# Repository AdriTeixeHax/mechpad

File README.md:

# :snowflake:Project MechPad:fire:
DIY, modular, split, open source mechanical keyboard and macro-pad with per-key RGB lighting, built around the ATMEGA-32U4 microcontroller.

## Features:
- Open source design.
- Swappable cherry-style mechanical switches.
- Aluminum casing.
- Modular design: detachable macro-pad with more room for expansion, attachable via magnets placed around the keyboard case.
- Rotary encoders to toggle programmable events, such as volume control or timeline scrolling for video editing software.
- OLED screen which displays layout information, battery status and other custom functions.
- Bluetooth integration.
- Easily swappable Li-Ion battery.
- Integrated 4-port USB hub, with downstream USB-A and USB-C ports.
- Per-key RGB lighting using WS2812(B) 5050 SMD LEDs.
- Ice-fire aesthetic.

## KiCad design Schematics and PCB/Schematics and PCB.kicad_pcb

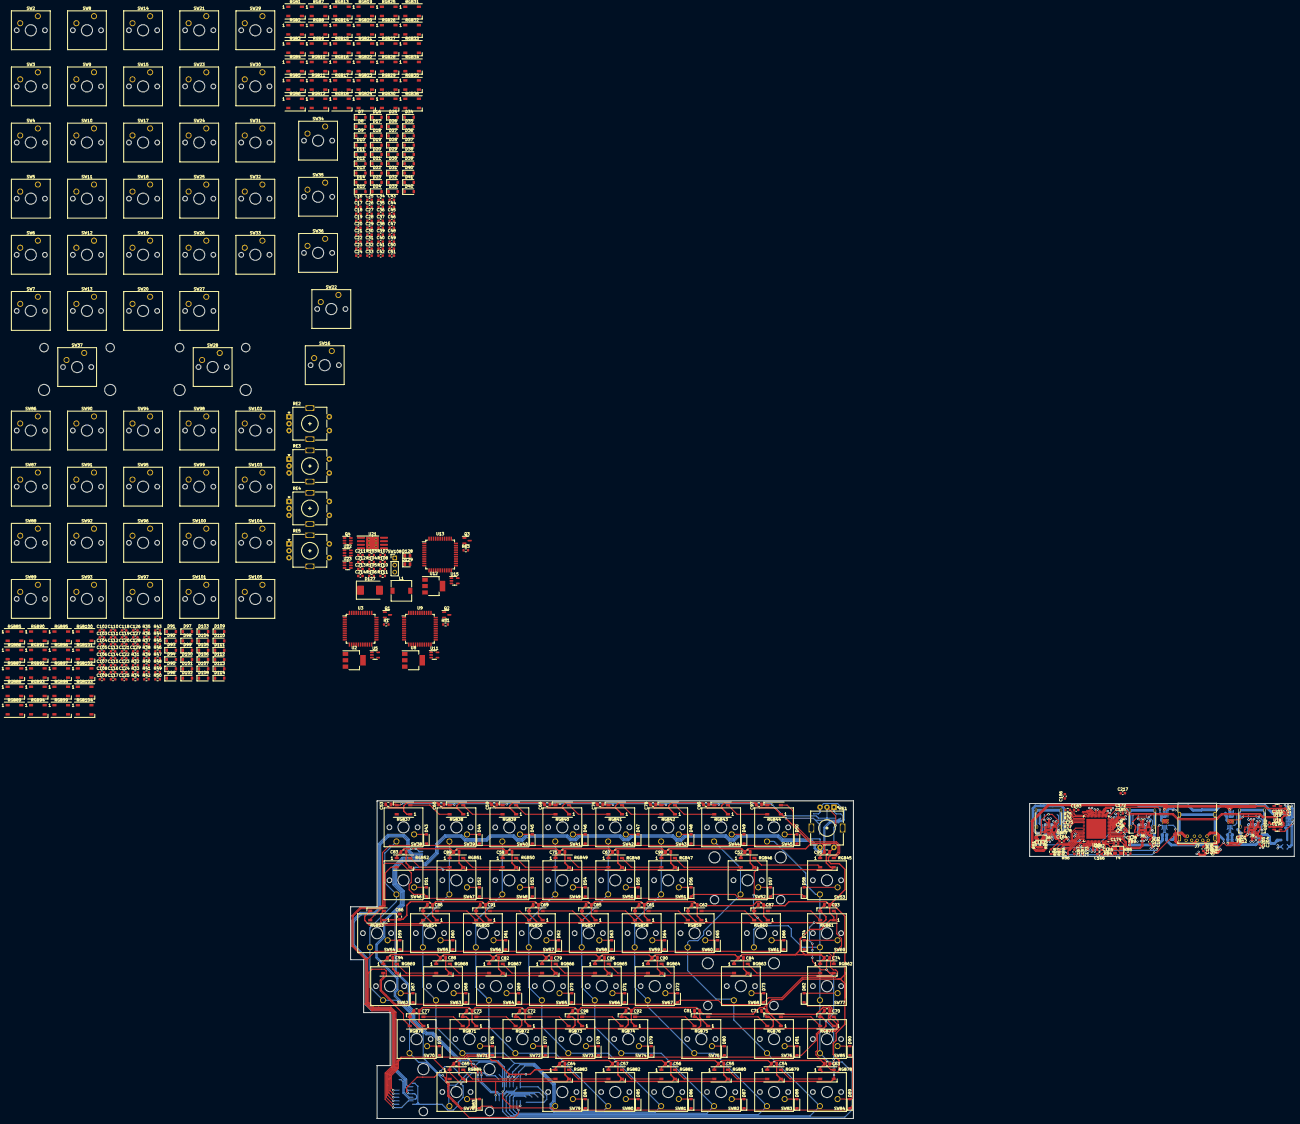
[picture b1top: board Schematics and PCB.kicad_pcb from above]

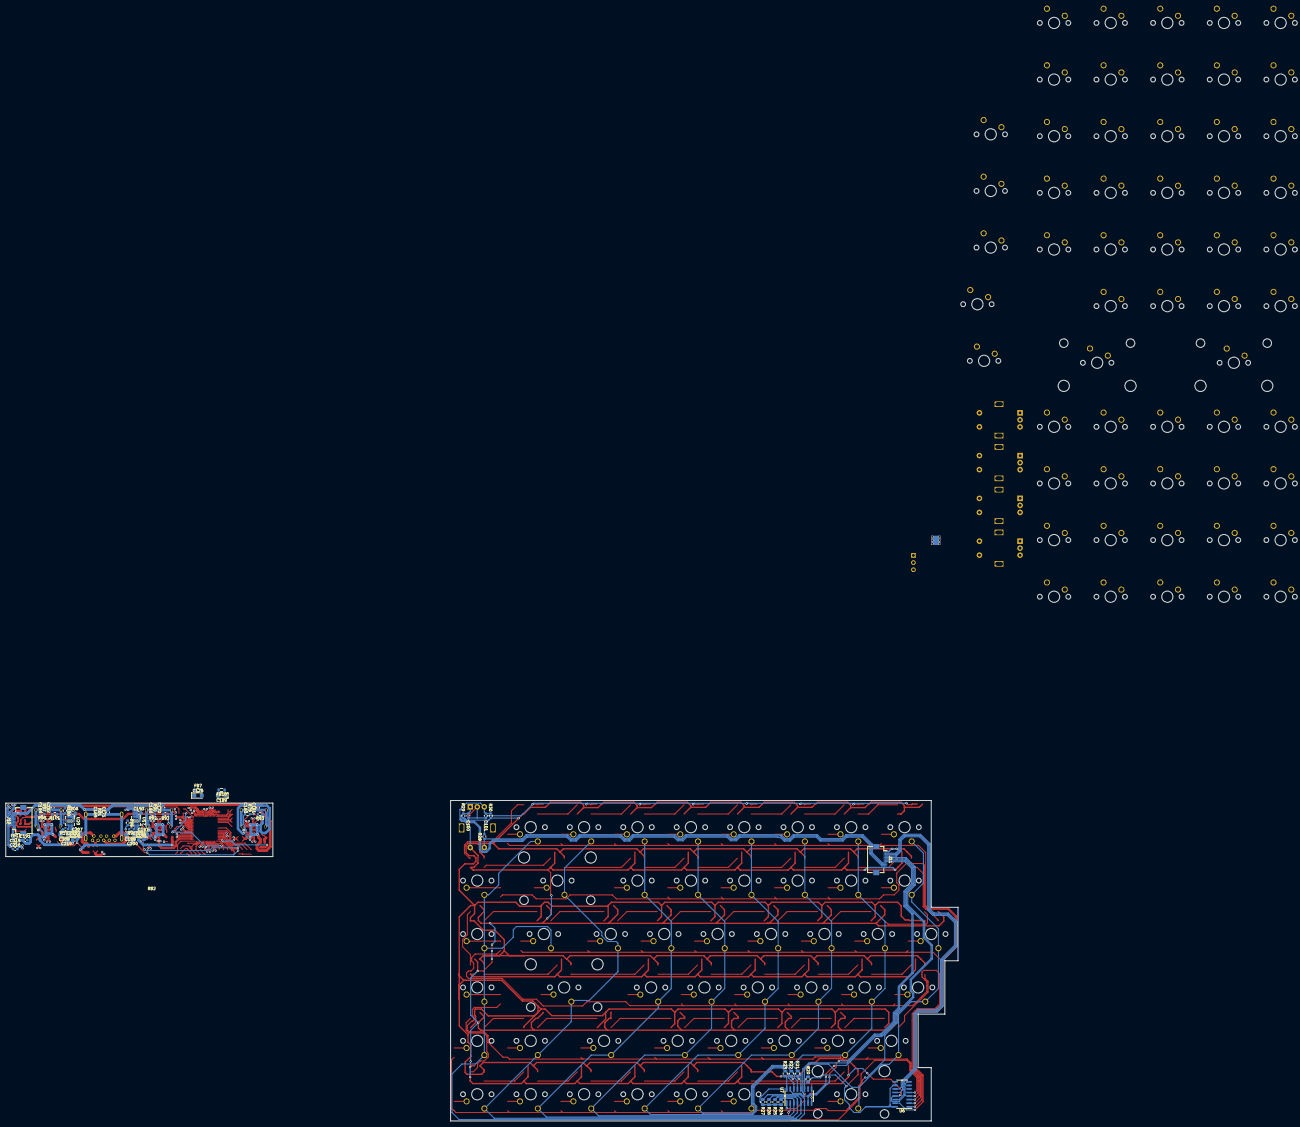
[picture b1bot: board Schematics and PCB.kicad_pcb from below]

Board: 4 copper layers, 339.6 x 114.3 mm, 604 parts (61 on the bottom side), 390 nets.

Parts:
C16, C17, C18, C19, C20, C21, C22, C23, C24, C25, C26, C27, C28, C29, C30, C31, C32, C33, C34, C35, C36, C37, C38, C39, C40, C41, C42, C43, C44, C45, C46, C47, C48, C49, C50, C51, C100, C101, C102, C103, C104, C105, C106, C107, C108, C109, C110, C111, C112, C113, C114, C115, C116, C117, C118, C119, C120, C121, C161, C163, C164, C170, C171, C172, C173, C174, C175, C177, C178, C179, C180, C181, C182, C183, C184, C185, C186, C187, C188, C190, C191, C193, C194, C198, C200, C201, C204, C205, C206, C208, C210, C214, C215, C216, C217: 100n; C_0603_1608Metric
C52, C53, C54, C55, C56, C57, C58, C59, C60, C61, C62, C63, C64, C65, C66, C67, C68, C69, C70, C71, C72, C73, C74, C75, C76, C77, C78, C79, C80, C81, C82, C83, C84, C85, C86, C87, C88, C89, C90, C91, C92, C93, C94, C95, C96, C97, C98, C99: 100n; C_0805_2012Metric
C122, C123, C124, C125, C126, C127, C128, C129: 10n; C_0603_1608Metric
C160, C168, C169, C192: 1n; C_0603_1608Metric
C162, C176, C189: 10u; CP_EIA-3216-18_Kemet-A
C165, C166: 20p; C_0603_1608Metric
C167: 1u; C_0603_1608Metric
C195, C196, C202, C203: 1u X5R; C_0603_1608Metric
C197, C199, C207, C209: 150u; CP_EIA-3216-18_Kemet-A
C211, C213: 22u; C_0603_1608Metric
C212: 10u; C_0603_1608Metric
D7, D8, D9, D10, D11, D12, D13, D14, D15, D16, D17, D18, D19, D20, D21, D22, D23, D24, D25, D26, D27, D28, D29, D30, D31, D32, D33, D34, D35, D36, D37, D38, D39, D40, D41, D42, D43, D44, D45, D46, D47, D48, D49, D50, D51, D52, D53, D54, D55, D56, D57, D58, D59, D60, D61, D62, D63, D64, D65, D66, D67, D68, D69, D70, D71, D72, D73, D74, D75, D76, D77, D78, D79, D80, D81, D82, D83, D84, D85, D86, D87, D88, D89, D90, D91, D92, D93, D94, D95, D96, D97, D98, D99, D100, D101, D102, D103, D104, D105, D106, D107, D108, D109, D110, D111, D112, D113, D114: 1N4148W; D_SOD-123
D127: SS34; D_SMC
D128: Red; LED_0805_2012Metric
D129: Green; LED_0805_2012Metric
FB7, FB8, FB9, FB10, FB11, FB12: >50mΩ 220Ω @ 100MHz; L_0805_2012Metric
J6: UPSTREAM; USB_C_Receptacle_Amphenol_12401610E4-2A
J7: DOWNSTREAM_3; USB3_A_Molex_48393-001
J8: DOWNSTREAM_1; USB_C_Receptacle_Amphenol_12401610E4-2A
J9: DOWNSTREAM_2; USB_C_Receptacle_Amphenol_12401610E4-2A
J10, J11: Conn_01x12; Hirose_FH12-12S-0.5SH_1x12-1MP_P0.50mm_Horizontal
L1: 22uH; L_7.3x7.3_H4.5
Q1, Q2, Q3: FDN340P; SOT-23
Q4: FS8205; SOT-23-6
R1, R51, R63, R79, R84, R90, R91, R97: 1M; R_0603_1608Metric
R20, R21, R22, R23, R24, R25, R26, R27: 10K; R_0805_2012Metric
R28, R86, R94, R95, R99, R100: 10k; R_0603_1608Metric
R29, R30, R31, R32, R33, R34, R35, R36, R37, R38, R39, R40, R41, R42, R43, R44, R45, R46, R47, R48, R49, R50: 10K; R_0603_1608Metric
R75, R76, R77, R78, R87, R88, R89: 4.7k; R_0603_1608Metric
R80: 90.9kΩ ±1%; R_0603_1608Metric
R81: 10kΩ ±1%; R_0603_1608Metric
R82, R83, R92, R93, R98, R101: 5.1k; R_0603_1608Metric
R85: 9.53kΩ ±1%; R_0603_1608Metric
R96, R102: 25.5k; R_0603_1608Metric
R103: 7.5K; R_0603_1608Metric
R104, R105, R106, R107, R108, R110, R111: 1k; R_0603_1608Metric
RE1, RE2, RE3, RE4, RE5: EC11; RotaryEncoder_Alps_EC11E-Switch_Vertical_H20mm
RGB1, RGB2, RGB3, RGB4, RGB5, RGB6, RGB7, RGB8, RGB9, RGB10, RGB11, RGB12, RGB13, RGB14, RGB15, RGB16, RGB17, RGB18, RGB19, RGB20, RGB21, RGB22, RGB23, RGB24, RGB25, RGB26, RGB27, RGB28, RGB29, RGB30, RGB31, RGB32, RGB33, RGB34, RGB35, RGB36, RGB37, RGB38, RGB39, RGB40, RGB41, RGB42, RGB43, RGB44, RGB45, RGB46, RGB47, RGB48, RGB49, RGB50, RGB51, RGB52, RGB53, RGB54, RGB55, RGB56, RGB57, RGB58, RGB59, RGB60, RGB61, RGB62, RGB63, RGB64, RGB65, RGB66, RGB67, RGB68, RGB69, RGB70, RGB71, RGB72, RGB73, RGB74, RGB75, RGB76, RGB77, RGB78, RGB79, RGB80, RGB81, RGB82, RGB83, RGB84, RGB85, RGB86, RGB87, RGB88, RGB89, RGB90, RGB91, RGB92, RGB93, RGB94, RGB95, RGB96, RGB97, RGB98, RGB99, RGB100, RGB101, RGB102, RGB103, RGB104: WS2812B; LED_WS2812B_PLCC4_5.0x5.0mm_P3.2mm
SW2: ESC; SW_Cherry_MX_1.00u_PCB
SW3: F1; SW_Cherry_MX_1.00u_PCB
SW4: F2; SW_Cherry_MX_1.00u_PCB
SW5: F3; SW_Cherry_MX_1.00u_PCB
SW6: F4; SW_Cherry_MX_1.00u_PCB
SW7: F5; SW_Cherry_MX_1.00u_PCB
SW8: F6; SW_Cherry_MX_1.00u_PCB
SW9: `; SW_Cherry_MX_1.00u_PCB
SW10: 1; SW_Cherry_MX_1.00u_PCB
SW11: 2; SW_Cherry_MX_1.00u_PCB
SW12: 3; SW_Cherry_MX_1.00u_PCB
SW13: 4; SW_Cherry_MX_1.00u_PCB
SW14: 5; SW_Cherry_MX_1.00u_PCB
SW15: 6; SW_Cherry_MX_1.00u_PCB
SW16: TAB; SW_Cherry_MX_1.50u_PCB
SW17: Q; SW_Cherry_MX_1.00u_PCB
SW18: W; SW_Cherry_MX_1.00u_PCB
SW19: E; SW_Cherry_MX_1.00u_PCB
SW20: R; SW_Cherry_MX_1.00u_PCB
SW21: T; SW_Cherry_MX_1.00u_PCB
SW22: MAYUS; SW_Cherry_MX_1.75u_PCB
SW23: A; SW_Cherry_MX_1.00u_PCB
SW24: S; SW_Cherry_MX_1.00u_PCB
SW25: D; SW_Cherry_MX_1.00u_PCB
SW26: F; SW_Cherry_MX_1.00u_PCB
SW27: G; SW_Cherry_MX_1.00u_PCB
SW28: L_SHIFT; SW_Cherry_MX_2.25u_PCB
SW29: Z; SW_Cherry_MX_1.00u_PCB
SW30: X; SW_Cherry_MX_1.00u_PCB
SW31: C; SW_Cherry_MX_1.00u_PCB
SW32: V; SW_Cherry_MX_1.00u_PCB
SW33: B; SW_Cherry_MX_1.00u_PCB
SW34: L_CRTL; SW_Cherry_MX_1.25u_PCB
SW35: OS; SW_Cherry_MX_1.25u_PCB
SW36: L_ALT; SW_Cherry_MX_1.25u_PCB
SW37: L_SPACE; SW_Cherry_MX_2.75u_PCB
SW38: F7; SW_Cherry_MX_1.00u_PCB
SW39: F8; SW_Cherry_MX_1.00u_PCB
SW40: F9; SW_Cherry_MX_1.00u_PCB
SW41: F10; SW_Cherry_MX_1.00u_PCB
SW42: F11; SW_Cherry_MX_1.00u_PCB
SW43: F12; SW_Cherry_MX_1.00u_PCB
SW44: PRT_SCR; SW_Cherry_MX_1.00u_PCB
SW45: DEL; SW_Cherry_MX_1.00u_PCB
SW46: 7; SW_Cherry_MX_1.00u_PCB
SW47: 8; SW_Cherry_MX_1.00u_PCB
SW48: 9; SW_Cherry_MX_1.00u_PCB
SW49: 0; SW_Cherry_MX_1.00u_PCB
SW50: -; SW_Cherry_MX_1.00u_PCB
SW51: =; SW_Cherry_MX_1.00u_PCB
SW52: BACKSPACE; SW_Cherry_MX_2.00u_PCB
SW53: MACRO1; SW_Cherry_MX_1.00u_PCB
SW54: Y; SW_Cherry_MX_1.00u_PCB
SW55: U; SW_Cherry_MX_1.00u_PCB
SW56: I; SW_Cherry_MX_1.00u_PCB
SW57: O; SW_Cherry_MX_1.00u_PCB
SW58: P; SW_Cherry_MX_1.00u_PCB
SW59: [; SW_Cherry_MX_1.00u_PCB
SW60: ]; SW_Cherry_MX_1.00u_PCB
SW61: \; SW_Cherry_MX_1.50u_PCB
SW62: H; SW_Cherry_MX_1.00u_PCB
SW63: J; SW_Cherry_MX_1.00u_PCB
SW64: K; SW_Cherry_MX_1.00u_PCB
SW65: L; SW_Cherry_MX_1.00u_PCB
SW66: ;; SW_Cherry_MX_1.00u_PCB
SW67: '; SW_Cherry_MX_1.00u_PCB
SW68: ENTER; SW_Cherry_MX_2.25u_PCB
SW69: MACRO2; SW_Cherry_MX_1.00u_PCB
SW70: N; SW_Cherry_MX_1.00u_PCB
SW71: M; SW_Cherry_MX_1.00u_PCB
SW72: ,; SW_Cherry_MX_1.00u_PCB
SW73: .; SW_Cherry_MX_1.00u_PCB
SW74: /; SW_Cherry_MX_1.00u_PCB
SW75: R_SHIFT; SW_Cherry_MX_1.75u_PCB
SW76: UP; SW_Cherry_MX_1.00u_PCB
SW77: MACRO3; SW_Cherry_MX_1.00u_PCB
SW78: R_SPACE; SW_Cherry_MX_2.75u_PCB
SW79: R_ALT; SW_Cherry_MX_1.00u_PCB
SW80: FN; SW_Cherry_MX_1.00u_PCB
SW81: R_CTRL; SW_Cherry_MX_1.00u_PCB
SW82: LEFT; SW_Cherry_MX_1.00u_PCB
SW83: DOWN; SW_Cherry_MX_1.00u_PCB
SW84: RIGHT; SW_Cherry_MX_1.00u_PCB
SW85: MACRO4; SW_Cherry_MX_1.00u_PCB
SW86: NUMPAD1; SW_Cherry_MX_1.00u_PCB
SW87: NUMPAD2; SW_Cherry_MX_1.00u_PCB
SW88: NUMPAD3; SW_Cherry_MX_1.00u_PCB
SW89: NUMPAD4; SW_Cherry_MX_1.00u_PCB
SW90: NUMPAD5; SW_Cherry_MX_1.00u_PCB
SW91: NUMPAD6; SW_Cherry_MX_1.00u_PCB
SW92: NUMPAD7; SW_Cherry_MX_1.00u_PCB
SW93: NUMPAD8; SW_Cherry_MX_1.00u_PCB
SW94: NUMPAD9; SW_Cherry_MX_1.00u_PCB
SW95: NUMPAD10; SW_Cherry_MX_1.00u_PCB
SW96: NUMPAD11; SW_Cherry_MX_1.00u_PCB
SW97: NUMPAD12; SW_Cherry_MX_1.00u_PCB
SW98: NUMPAD13; SW_Cherry_MX_1.00u_PCB
SW99: NUMPAD14; SW_Cherry_MX_1.00u_PCB
SW100: NUMPAD15; SW_Cherry_MX_1.00u_PCB
SW101: NUMPAD16; SW_Cherry_MX_1.00u_PCB
SW102: NUMPAD17; SW_Cherry_MX_1.00u_PCB
SW103: NUMPAD18; SW_Cherry_MX_1.00u_PCB
SW104: NUMPAD19; SW_Cherry_MX_1.00u_PCB
SW105: NUMPAD20; SW_Cherry_MX_1.00u_PCB
SW108: Battery Switch; PinHeader_1x03_P2.54mm_Vertical
U2, U8, U12: NCP1117ST50T3G; SOT-223-3_TabPin2
U3, U9, U13: ATmega32U4; TQFP-44_10x10mm_P0.8mm
U5, U11, U15: LP2985-33DBVR; SOT-23-5
U6: SOP-16_3.9x9.9mm_P1.27mm
U7: 74HC165; SOP-16_3.9x9.9mm_P1.27mm
U16: TUSB8042A; VQFN-64-1EP_9x9mm_P0.5mm_EP7.15x7.15mm
U17, U20: TPS2561; VSON-10-1EP_3x3mm_P0.5mm_EP1.65x2.4mm_ThermalVias
U18: TLV71311PDBVR; TSOT-23-5
U19: TLV70033DDCR; TSOT-23-5
U21: TP4056; SOP-8-1EP_4.57x4.57mm_P1.27mm_EP4.57x4.45mm_ThermalVias
U22: MT3608; SOT-23-6
U23: FS312F-G; SOT-23-6
Y4: 24MHz 20pF GND24; Crystal_SMD_3225-4Pin_3.2x2.5mm

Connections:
+3V3: C203.1, FB7.1, R75.2, R76.2, R77.2, R78.2, R94.1, R95.1, R99.1, R100.1, U5.5 (VOUT), U11.5 (VOUT), U15.5 (VOUT), U19.5 (VOUT)
+5V: C16.1, C17.1, C18.1, C19.1, C20.1, C21.1, C22.1, C23.1, C24.1, C25.1, C26.1, C27.1, C28.1, C29.1, C30.1, C31.1, C32.1, C33.1, C34.1, C35.1, C36.1, C37.1, C38.1, C39.1, C40.1, C41.1, C42.1, C43.1, C44.1, C45.1, C46.1, C47.1, C48.1, C49.1, C50.1, C51.1, C52.1, C53.1, C54.1, C55.1, C56.1, C57.1, C58.1, C59.1, C60.1, C61.1, C62.1, C63.1, C64.1, C65.1, C66.1, C67.1, C68.1, C69.1, C70.1, C71.1, C72.1, C73.1, C74.1, C75.1, C76.1, C77.1, C78.1, C79.1, C80.1, C81.1, C82.1, C83.1, C84.1, C85.1, C86.1, C87.1, C88.1, C89.1, C90.1, C91.1, C92.1, C93.1, C94.1, C95.1, C96.1, C97.1, C98.1, C99.1, C102.1, C103.1, C104.1, C105.1, C106.1, C107.1, C108.1, C109.1, C110.1, C111.1, C112.1, C113.1, C114.1, C115.1, C116.1, C117.1, C118.1, C119.1, C120.1, C121.1, C211.2, D127.1 (K), J11.1, Q1.2 (S), Q2.2 (S), Q3.2 (S), R20.1, R21.1, R22.1, R23.1, R24.1, R25.1, R26.1, R27.1, R28.1, R29.1, R30.1, R31.1, R32.1, R33.1, R34.1, R35.1, R36.1, R37.1, R38.1, R47.1, R48.1, R49.1, R50.1, R103.1, RGB1.1 (VDD), RGB2.1 (VDD), RGB3.1 (VDD), RGB4.1 (VDD), RGB5.1 (VDD), RGB6.1 (VDD), RGB7.1 (VDD), RGB8.1 (VDD), RGB9.1 (VDD), RGB10.1 (VDD), RGB11.1 (VDD), RGB12.1 (VDD), RGB13.1 (VDD), RGB14.1 (VDD), RGB15.1 (VDD), RGB16.1 (VDD), RGB17.1 (VDD), RGB18.1 (VDD), RGB19.1 (VDD), RGB20.1 (VDD), RGB21.1 (VDD), RGB22.1 (VDD), RGB23.1 (VDD), RGB24.1 (VDD), RGB25.1 (VDD), RGB26.1 (VDD), RGB27.1 (VDD), RGB28.1 (VDD), RGB29.1 (VDD), RGB30.1 (VDD), RGB31.1 (VDD), RGB32.1 (VDD), RGB33.1 (VDD), RGB34.1 (VDD), RGB35.1 (VDD), RGB36.1 (VDD), RGB37.1 (VDD), RGB38.1 (VDD), RGB39.1 (VDD), RGB40.1 (VDD), RGB41.1 (VDD), RGB42.1 (VDD), RGB43.1 (VDD), RGB44.1 (VDD), RGB45.1 (VDD), RGB46.1 (VDD), RGB47.1 (VDD), RGB48.1 (VDD), RGB49.1 (VDD), RGB50.1 (VDD), RGB51.1 (VDD), RGB52.1 (VDD), RGB53.1 (VDD), RGB54.1 (VDD), RGB55.1 (VDD), RGB56.1 (VDD), RGB57.1 (VDD), RGB58.1 (VDD), RGB59.1 (VDD), RGB60.1 (VDD), RGB61.1 (VDD), RGB62.1 (VDD), RGB63.1 (VDD), RGB64.1 (VDD), RGB65.1 (VDD), RGB66.1 (VDD), RGB67.1 (VDD), RGB68.1 (VDD), RGB69.1 (VDD), RGB70.1 (VDD), RGB71.1 (VDD), RGB72.1 (VDD), RGB73.1 (VDD), RGB74.1 (VDD), RGB75.1 (VDD), RGB76.1 (VDD), RGB77.1 (VDD), RGB78.1 (VDD), RGB79.1 (VDD), RGB80.1 (VDD), RGB81.1 (VDD), RGB82.1 (VDD), RGB83.1 (VDD), RGB84.1 (VDD), RGB85.1 (VDD), RGB86.1 (VDD), RGB87.1 (VDD), RGB88.1 (VDD), RGB89.1 (VDD), RGB90.1 (VDD), RGB91.1 (VDD), RGB92.1 (VDD), RGB93.1 (VDD), RGB94.1 (VDD), RGB95.1 (VDD), RGB96.1 (VDD), RGB97.1 (VDD), RGB98.1 (VDD), RGB99.1 (VDD), RGB100.1 (VDD), RGB101.1 (VDD), RGB102.1 (VDD), RGB103.1 (VDD), RGB104.1 (VDD), U2.2 (VO), U3.2 (UVCC), U3.14 (VCC), U3.34 (VCC), U5.1 (VIN), U5.3 (ON/~OFF), U6.10 (~CLR), U6.16 (VCC), U7.16 (VCC), U8.2 (VO), U8.3 (VI), U9.2 (UVCC), U9.14 (VCC), U9.34 (VCC), U11.1 (VIN), U11.3 (ON/~OFF), U12.2 (VO), U13.2 (UVCC), U13.14 (VCC), U13.34 (VCC), U15.1 (VIN), U15.3 (ON/~OFF)
/CP: J11.5, U7.2 (CP), U9.25 (PD4)
/DS: J11.2, U6.14 (DS), U9.28 (PB4)
/Left Switch Matrix/COL_0_L: SW2.1 (A), SW9.1 (A), SW16.1 (A), SW22.1 (A), SW28.1 (A), SW34.1 (A)
/Left Switch Matrix/COL_1_L: SW3.1 (A), SW10.1 (A), SW17.1 (A), SW23.1 (A), SW29.1 (A), SW35.1 (A)
/Left Switch Matrix/COL_2_L: SW4.1 (A), SW11.1 (A), SW18.1 (A), SW24.1 (A), SW30.1 (A), SW36.1 (A)
/Left Switch Matrix/COL_3_L: SW5.1 (A), SW12.1 (A), SW19.1 (A), SW25.1 (A), SW31.1 (A), SW37.1 (A)
/Left Switch Matrix/COL_4_L: SW6.1 (A), SW13.1 (A), SW20.1 (A), SW26.1 (A), SW32.1 (A)
/Left Switch Matrix/COL_5_L: SW7.1 (A), SW14.1 (A), SW21.1 (A), SW27.1 (A), SW33.1 (A)
/Left Switch Matrix/COL_6_L: SW8.1 (A), SW15.1 (A)
/Left Switch Matrix/RGB_IN_L: RGB1.4 (DIN), U3.18 (PD0)
/Left Switch Matrix/ROW_0_L: D7.1 (K), D8.1 (K), D9.1 (K), D10.1 (K), D11.1 (K), D12.1 (K), D13.1 (K), U3.36 (PF7)
/Left Switch Matrix/ROW_1_L: D14.1 (K), D15.1 (K), D16.1 (K), D17.1 (K), D18.1 (K), D19.1 (K), D20.1 (K), U3.37 (PF6)
/Left Switch Matrix/ROW_2_L: D21.1 (K), D22.1 (K), D23.1 (K), D24.1 (K), D25.1 (K), D26.1 (K), U3.38 (PF5)
/Left Switch Matrix/ROW_3_L: D27.1 (K), D28.1 (K), D29.1 (K), D30.1 (K), D31.1 (K), D32.1 (K), U3.39 (PF4)
/Left Switch Matrix/ROW_4_L: D33.1 (K), D34.1 (K), D35.1 (K), D36.1 (K), D37.1 (K), D38.1 (K), U3.40 (PF1)
/Left Switch Matrix/ROW_5_L: D39.1 (K), D40.1 (K), D41.1 (K), D42.1 (K), U3.41 (PF0)
/Main IC1/AVCC: U9.24 (AVCC), U9.44 (AVCC)
/Main IC1/D11#: RGB37.4 (DIN), U9.12 (PB7)
/Main IC1/VUSB: Q2.3 (D), U9.7 (VBUS)
/Main IC1/XTAL1: R51.2, U9.17 (XTAL1)
/Main IC1/XTAL2: R51.1, U9.16 (XTAL2)
/Main IC2/A0: D91.1 (K), D92.1 (K), D93.1 (K), D94.1 (K), U13.36 (PF7)
/Main IC2/A1: D95.1 (K), D96.1 (K), D97.1 (K), D98.1 (K), U13.37 (PF6)
/Main IC2/A2: D99.1 (K), D100.1 (K), D101.1 (K), D102.1 (K), U13.38 (PF5)
/Main IC2/A3: D103.1 (K), D104.1 (K), D105.1 (K), D106.1 (K), U13.39 (PF4)
/Main IC2/A4: D107.1 (K), D108.1 (K), D109.1 (K), D110.1 (K), U13.40 (PF1)
/Main IC2/A5: D111.1 (K), D112.1 (K), D113.1 (K), D114.1 (K), U13.41 (PF0)
/Main IC2/AVCC: U13.24 (AVCC), U13.44 (AVCC)
/Main IC2/D9#: RGB85.4 (DIN), U13.29 (PB5)
/Main IC2/D13#: R50.2, RE5.S1, SW89.1 (A), SW93.1 (A), SW97.1 (A), SW101.1 (A), SW105.1 (A), U13.32 (PC7)
/Main IC2/VUSB: Q3.3 (D), U13.7 (VBUS)
/Main IC2/XTAL1: R63.2, U13.17 (XTAL1)
/Main IC2/XTAL2: R63.1, U13.16 (XTAL2)
/Main IC/AVCC: U3.24 (AVCC), U3.44 (AVCC)
/Main IC/VUSB: Q1.3 (D), U3.7 (VBUS)
/Main IC/XTAL1: R1.2, U3.17 (XTAL1)
/Main IC/XTAL2: R1.1, U3.16 (XTAL2)
/Numpad Switch Matrix/RE_1_A: C123.1, R40.2
/Numpad Switch Matrix/RE_1_B: C122.1, R39.2
/Numpad Switch Matrix/RE_2_A: C125.1, R42.2
/Numpad Switch Matrix/RE_2_B: C124.1, R41.2
/Numpad Switch Matrix/RE_3_A: C127.1, R44.2
/Numpad Switch Matrix/RE_3_B: C126.1, R43.2
/Numpad Switch Matrix/RE_4_A: C129.1, R46.2
/Numpad Switch Matrix/RE_4_B: C128.1, R45.2
/Numpad Switch Matrix/SW1.1: R48.2, RE2.S1, SW86.1 (A), SW90.1 (A), SW94.1 (A), SW98.1 (A), SW102.1 (A), U13.30 (PB6)
/Numpad Switch Matrix/SW1.2: D91.2 (A), RE2.S2
/Numpad Switch Matrix/SW2.1: R47.2, RE3.S1, SW87.1 (A), SW91.1 (A), SW95.1 (A), SW99.1 (A), SW103.1 (A), U13.12 (PB7)
/Numpad Switch Matrix/SW2.2: D92.2 (A), RE3.S2
/Numpad Switch Matrix/SW3.1: R49.2, RE4.S1, SW88.1 (A), SW92.1 (A), SW96.1 (A), SW100.1 (A), SW104.1 (A), U13.26 (PD6)
/Numpad Switch Matrix/SW3.2: D93.2 (A), RE4.S2
/Numpad Switch Matrix/SW4.2: D94.2 (A), RE5.S2
/RE_1_A: C101.1, J11.11, R30.2, RE1.B, U9.26 (PD6)
/RE_1_B: C100.1, J11.10, R29.2, RE1.A, U9.32 (PC7)
/RE_SW: J11.9, R28.2, RE1.S1, U9.36 (PF7)
/Right Switch Matrix/COL_0_R: R20.2, SW38.1 (A), SW46.1 (A), SW54.1 (A), SW62.1 (A), SW70.1 (A), SW78.1 (A), U7.11 (D0)
/Right Switch Matrix/COL_1_R: R21.2, SW39.1 (A), SW47.1 (A), SW55.1 (A), SW63.1 (A), SW71.1 (A), SW79.1 (A), U7.12 (D1)
/Right Switch Matrix/COL_2_R: R22.2, SW40.1 (A), SW48.1 (A), SW56.1 (A), SW64.1 (A), SW72.1 (A), SW80.1 (A), U7.13 (D2)
/Right Switch Matrix/COL_3_R: R23.2, SW41.1 (A), SW49.1 (A), SW57.1 (A), SW65.1 (A), SW73.1 (A), SW81.1 (A), U7.14 (D3)
/Right Switch Matrix/COL_4_R: R24.2, SW42.1 (A), SW50.1 (A), SW58.1 (A), SW66.1 (A), SW74.1 (A), SW82.1 (A), U7.3 (D4)
/Right Switch Matrix/COL_5_R: R25.2, SW43.1 (A), SW51.1 (A), SW59.1 (A), SW67.1 (A), SW75.1 (A), SW83.1 (A), U7.4 (D5)
/Right Switch Matrix/COL_6_R: R26.2, SW44.1 (A), SW52.1 (A), SW60.1 (A), SW68.1 (A), SW76.1 (A), SW84.1 (A), U7.5 (D6)
/Right Switch Matrix/COL_7_R: R27.2, SW45.1 (A), SW53.1 (A), SW61.1 (A), SW69.1 (A), SW77.1 (A), SW85.1 (A), U7.6 (D7)
/Right Switch Matrix/ROW_0_R: D43.1 (K), D44.1 (K), D45.1 (K), D46.1 (K), D47.1 (K), D48.1 (K), D49.1 (K), D50.1 (K), U6.15 (QA)
/Right Switch Matrix/ROW_1_R: D51.1 (K), D52.1 (K), D53.1 (K), D54.1 (K), D55.1 (K), D56.1 (K), D57.1 (K), D58.1 (K), U6.1 (QB)
/Right Switch Matrix/ROW_2_R: D59.1 (K), D60.1 (K), D61.1 (K), D62.1 (K), D63.1 (K), D64.1 (K), D65.1 (K), D66.1 (K), U6.2 (QC)
/Right Switch Matrix/ROW_3_R: D67.1 (K), D68.1 (K), D69.1 (K), D70.1 (K), D71.1 (K), D72.1 (K), D73.1 (K), D74.1 (K), U6.3 (QD)
/Right Switch Matrix/ROW_4_R: D75.1 (K), D76.1 (K), D77.1 (K), D78.1 (K), D79.1 (K), D80.1 (K), D81.1 (K), D82.1 (K), U6.4 (QE)
/Right Switch Matrix/ROW_5_R: D83.1 (K), D84.1 (K), D85.1 (K), D86.1 (K), D87.1 (K), D88.1 (K), D89.1 (K), D90.1 (K), U6.5 (QF)
/SH_CP: J11.4, U6.11 (SH_CP), U9.30 (PB6)
/ST_CP: J11.3, U6.12 (ST_CP), U9.29 (PB5)
/USB Hub/1V1_EN: J10.5, U18.3 (EN)
/USB Hub/1V1_HUB: C196.1, FB10.1, U18.5 (VOUT)
/USB Hub/1V1_HUB_FILTER: C182.1, C183.1, C184.1, C185.1, C186.1, C187.1, C188.1, C189.1, C217.1, FB10.2, U16.5 (VDD), U16.8 (VDD), U16.13 (VDD), U16.21 (VDD), U16.28 (VDD), U16.31 (VDD), U16.51 (VDD), U16.57 (VDD)
/USB Hub/3V3_EN: J10.6, U19.3 (EN)
/USB Hub/3V3_HUB_FILTER: C172.1, C173.1, C174.1, C175.1, C176.1, FB7.2, U16.16 (VDD33), U16.34 (VDD33), U16.52 (VDD33), U16.63 (VDD33)
/USB Hub/BAT_EN_1: R78.1, U16.36 (PWRCTL1/BATEN1), U17.4 (EN1)
/USB Hub/BAT_EN_2: R77.1, U16.35 (PWRCTL2/BATEN2), U17.5 (EN2)
/USB Hub/BAT_EN_3: R76.1, U16.33 (PWRCTL3/BATEN3), U20.4 (EN1)
/USB Hub/BAT_EN_4: R75.1, U16.32 (PWRCTL4/BATEN4), U20.5 (EN2)
/USB Hub/DN1_N: J8.A7 (D-), J8.B7 (D-), U16.2 (USB_DM_DN1)
/USB Hub/DN1_P: J8.A6 (D+), J8.B6 (D+), U16.1 (USB_DP_DN1)
/USB Hub/DN1_SSRX_N: J8.B10 (RX1-), U16.7 (USB_SSRXM_DN1)
/USB Hub/DN1_SSRX_P: J8.B11 (RX1+), U16.6 (USB_SSRXP_DN1)
/USB Hub/DN1_SSTX_CAP_N: C190.1, J8.A3 (TX1-)
/USB Hub/DN1_SSTX_CAP_P: C181.1, J8.A2 (TX1+)
/USB Hub/DN1_SSTX_N: C190.2, U16.4 (USB_SSTXM_DN1)
/USB Hub/DN1_SSTX_P: C181.2, U16.3 (USB_SSTXP_DN1)
/USB Hub/DN1_VBUS: C178.1, C197.1, C198.1, FB9.2, U17.9 (OUT1)
/USB Hub/DN2_N: J7.2 (D-), U16.10 (USB_DM_DN2)
/USB Hub/DN2_P: J7.3 (D+), U16.9 (USB_DP_DN2)
/USB Hub/DN2_SSRX_N: J7.5 (RX-), U16.15 (USB_SSRXM_DN2)
/USB Hub/DN2_SSRX_P: J7.6 (RX+), U16.14 (USB_SSRXP_DN2)
/USB Hub/DN2_SSTX_CAP_N: C180.1, J7.8 (TX-)
/USB Hub/DN2_SSTX_CAP_P: C179.1, J7.9 (TX+)
/USB Hub/DN2_SSTX_N: C180.2, U16.12 (USB_SSTXM_DN2)
/USB Hub/DN2_SSTX_P: C179.2, U16.11 (USB_SSTXP_DN2)
/USB Hub/DN2_VBUS: C177.1, C199.1, C200.1, FB8.2, U17.8 (OUT2)
/USB Hub/DN3_N: J9.A7 (D-), J9.B7 (D-), U16.18 (USB_DM_DN3)
/USB Hub/DN3_P: J9.A6 (D+), J9.B6 (D+), U16.17 (USB_DP_DN3)
/USB Hub/DN3_SSRX_N: J9.B10 (RX1-), U16.23 (USB_SSRXM_DN3)
/USB Hub/DN3_SSRX_P: J9.B11 (RX1+), U16.22 (USB_SSRXP_DN3)
/USB Hub/DN3_SSTX_CAP_N: C205.1, J9.A3 (TX1-)
/USB Hub/DN3_SSTX_CAP_P: C204.1, J9.A2 (TX1+)
/USB Hub/DN3_SSTX_N: C205.2, U16.20 (USB_SSTXM_DN3)
/USB Hub/DN3_SSTX_P: C204.2, U16.19 (USB_SSTXP_DN3)
/USB Hub/DN3_VBUS: C201.1, C207.1, C208.1, FB12.2, U20.9 (OUT1)
/USB Hub/DN4_CONN: FB11.1, J10.1, J10.2
/USB Hub/DN4_N: J10.8, U16.25 (USB_DM_DN4)
/USB Hub/DN4_P: J10.7, U16.24 (USB_DP_DN4)
/USB Hub/DN4_SSRX_N: J10.10, U16.30 (USB_SSRXM_DN4)
/USB Hub/DN4_SSRX_P: J10.9, U16.29 (USB_SSRXP_DN4)
/USB Hub/DN4_SSTX_CAP_N: C216.1, J10.4
/USB Hub/DN4_SSTX_CAP_P: C215.1, J10.3
/USB Hub/DN4_SSTX_N: C216.2, U16.27 (USB_SSTXM_DN4)
/USB Hub/DN4_SSTX_P: C215.2, U16.26 (USB_SSTXP_DN4)
/USB Hub/DN4_VBUS: C191.1, C209.1, C210.1, FB11.2, U20.8 (OUT2)
/USB Hub/UP_N: J6.A7 (D-), J6.B7 (D-), U16.54 (USB_DM_UP)
/USB Hub/UP_P: J6.A6 (D+), J6.B6 (D+), U16.53 (USB_DP_UP)
/USB Hub/UP_SSRX_N: J6.B10 (RX1-), U16.59 (USB_SSRXM_UP)
/USB Hub/UP_SSRX_P: J6.B11 (RX1+), U16.58 (USB_SSRXP_UP)
/USB Hub/UP_SSTX_CAP_N: C164.1, J6.A3 (TX1-)
/USB Hub/UP_SSTX_CAP_P: C163.1, J6.A2 (TX1+)
/USB Hub/UP_SSTX_N: C164.2, U16.56 (USB_SSTXM_UP)
/USB Hub/UP_SSTX_P: C163.2, U16.55 (USB_SSTXP_UP)
/USB Hub/UP_VBUS: C162.1, C193.1, C195.1, C202.1, C206.1, J6.A4 (VBUS), J6.A9 (VBUS), J6.B4 (VBUS), J6.B9 (VBUS), R80.1, U17.2 (IN), U17.3 (IN), U18.2 (VIN), U19.2 (VIN), U20.2 (IN), U20.3 (IN)
/USB Hub/VBUS_IC: R80.2, R81.1, U16.48 (USB_VBUS)
/USB Hub/XI: C165.1, R84.1, U16.62 (XI), Y4.1
/USB Hub/XO: C166.1, R84.2, U16.61 (XO), Y4.3
/USB Hub/~OVCURR1: R94.2, U16.46 (OVERCUR1z), U17.10 (~FAULT1)
/USB Hub/~OVCURR2: R95.2, U16.47 (OVERCUR2z), U17.6 (~FAULT2)
/USB Hub/~OVCURR3: R99.2, U16.44 (OVERCUR3z), U20.10 (~FAULT1)
/USB Hub/~OVCURR4: R100.2, U16.43 (OVERCUR4z), U20.6 (~FAULT2)
/V_USB: C212.1, D128.2 (A), D129.2 (A), U21.4 (VCC), U21.8 (CE)
/~CE: J11.6, U7.15 (~CE), U9.31 (PC6)
/~PL: J11.7, U7.1 (~PL), U9.27 (PD7)
/~Q7: J11.8, U7.7 (~Q7), U9.1 (PE6)
GND: C16.2, C17.2, C18.2, C19.2, C20.2, C21.2, C22.2, C23.2, C24.2, C25.2, C26.2, C27.2, C28.2, C29.2, C30.2, C31.2, C32.2, C33.2, C34.2, C35.2, C36.2, C37.2, C38.2, C39.2, C40.2, C41.2, C42.2, C43.2, C44.2, C45.2, C46.2, C47.2, C48.2, C49.2, C50.2, C51.2, C52.2, C53.2, C54.2, C55.2, C56.2, C57.2, C58.2, C59.2, C60.2, C61.2, C62.2, C63.2, C64.2, C65.2, C66.2, C67.2, C68.2, C69.2, C70.2, C71.2, C72.2, C73.2, C74.2, C75.2, C76.2, C77.2, C78.2, C79.2, C80.2, C81.2, C82.2, C83.2, C84.2, C85.2, C86.2, C87.2, C88.2, C89.2, C90.2, C91.2, C92.2, C93.2, C94.2, C95.2, C96.2, C97.2, C98.2, C99.2, C100.2, C101.2, C102.2, C103.2, C104.2, C105.2, C106.2, C107.2, C108.2, C109.2, C110.2, C111.2, C112.2, C113.2, C114.2, C115.2, C116.2, C117.2, C118.2, C119.2, C120.2, C121.2, C122.2, C123.2, C124.2, C125.2, C126.2, C127.2, C128.2, C129.2, C160.2, C161.2, C162.2, C165.2, C166.2, C167.2, C168.2, C169.2, C170.2, C171.2, C172.2, C173.2, C174.2, C175.2, C176.2, C177.2, C178.2, C182.2, C183.2, C184.2, C185.2, C186.2, C187.2, C188.2, C189.2, C191.2, C192.2, C193.2, C194.2, C195.2, C196.2, C197.2, C198.2, C199.2, C200.2, C201.2, C202.2, C203.2, C206.2, C207.2, C208.2, C209.2, C210.2, C211.1, C212.2, C213.1, C217.2, J6.A1 (GND), J6.A12 (GND), J6.B1 (GND), J6.B12 (GND), J7.4 (GND), J7.7 (GND_DRAIN), J8.A1 (GND), J8.A12 (GND), J8.B1 (GND), J8.B12 (GND), J9.A1 (GND), J9.A12 (GND), J9.B1 (GND), J9.B12 (GND), J10.11, J10.12, J11.12, Q4.1, R79.2, R81.2, R82.2, R83.1, R85.2, R86.2, R87.2, R88.2, R89.2, R90.2, R91.2, R92.2, R93.1, R96.2, R97.2, R98.2, R101.1, R102.2, R107.2, R108.2, R111.1, RE1.C, RE1.S2, RE2.C, RE3.C, RE4.C, RE5.C, RGB1.3 (VSS), RGB2.3 (VSS), RGB3.3 (VSS), RGB4.3 (VSS), RGB5.3 (VSS), RGB6.3 (VSS), RGB7.3 (VSS), RGB8.3 (VSS), RGB9.3 (VSS), RGB10.3 (VSS), RGB11.3 (VSS), RGB12.3 (VSS), RGB13.3 (VSS), RGB14.3 (VSS), RGB15.3 (VSS), RGB16.3 (VSS), RGB17.3 (VSS), RGB18.3 (VSS), RGB19.3 (VSS), RGB20.3 (VSS), RGB21.3 (VSS), RGB22.3 (VSS), RGB23.3 (VSS), RGB24.3 (VSS), RGB25.3 (VSS), RGB26.3 (VSS), RGB27.3 (VSS), RGB28.3 (VSS), RGB29.3 (VSS), RGB30.3 (VSS), RGB31.3 (VSS), RGB32.3 (VSS), RGB33.3 (VSS), RGB34.3 (VSS), RGB35.3 (VSS), RGB36.3 (VSS), RGB37.3 (VSS), RGB38.3 (VSS), RGB39.3 (VSS), RGB40.3 (VSS), RGB41.3 (VSS), RGB42.3 (VSS), RGB43.3 (VSS), RGB44.3 (VSS), RGB45.3 (VSS), RGB46.3 (VSS), RGB47.3 (VSS), RGB48.3 (VSS), RGB49.3 (VSS), RGB50.3 (VSS), RGB51.3 (VSS), RGB52.3 (VSS), RGB53.3 (VSS), RGB54.3 (VSS), RGB55.3 (VSS), RGB56.3 (VSS), RGB57.3 (VSS), RGB58.3 (VSS), RGB59.3 (VSS), RGB60.3 (VSS), RGB61.3 (VSS), RGB62.3 (VSS), RGB63.3 (VSS), RGB64.3 (VSS), RGB65.3 (VSS), RGB66.3 (VSS), RGB67.3 (VSS), RGB68.3 (VSS), RGB69.3 (VSS), RGB70.3 (VSS), RGB71.3 (VSS), RGB72.3 (VSS), RGB73.3 (VSS), RGB74.3 (VSS), RGB75.3 (VSS), RGB76.3 (VSS), RGB77.3 (VSS), RGB78.3 (VSS), RGB79.3 (VSS), RGB80.3 (VSS), RGB81.3 (VSS), RGB82.3 (VSS), RGB83.3 (VSS), RGB84.3 (VSS), RGB85.3 (VSS), RGB86.3 (VSS), RGB87.3 (VSS), RGB88.3 (VSS), RGB89.3 (VSS), RGB90.3 (VSS), RGB91.3 (VSS), RGB92.3 (VSS), RGB93.3 (VSS), RGB94.3 (VSS), RGB95.3 (VSS), RGB96.3 (VSS), RGB97.3 (VSS), RGB98.3 (VSS), RGB99.3 (VSS), RGB100.3 (VSS), RGB101.3 (VSS), RGB102.3 (VSS), RGB103.3 (VSS), RGB104.3 (VSS), U2.1 (GND), U3.5 (UGND), U3.15 (GND), U3.23 (GND), U3.35 (GND), U5.2 (GND), U6.8 (GND), U6.13 (~OE), U7.8 (GND), U8.1 (GND), U9.5 (UGND), U9.15 (GND), U9.23 (GND), U9.35 (GND), U11.2 (GND), U12.1 (GND), U13.5 (UGND), U13.15 (GND), U13.23 (GND), U13.35 (GND), U15.2 (GND), U16.65 (THERMAL_PAD), U17.1 (GND), U17.11 (PAD), U18.1 (GND), U19.1 (GND), U20.1 (GND), U20.11 (PAD), U21.1 (TEMP), U21.3 (GND), U22.2 (GND), Y4.2, Y4.4
unnamed: SW108.1 (A), U21.5 (BAT)
unnamed: C214.1, Q4.3, U23.6 (GND)
unnamed: D7.2 (A), SW2.2 (B)
unnamed: D8.2 (A), SW3.2 (B)
unnamed: D9.2 (A), SW4.2 (B)
unnamed: D10.2 (A), SW5.2 (B)
unnamed: D11.2 (A), SW6.2 (B)
unnamed: D12.2 (A), SW7.2 (B)
unnamed: D13.2 (A), SW8.2 (B)
unnamed: D14.2 (A), SW9.2 (B)
unnamed: D15.2 (A), SW10.2 (B)
unnamed: D16.2 (A), SW11.2 (B)
unnamed: D17.2 (A), SW12.2 (B)
unnamed: D18.2 (A), SW13.2 (B)
unnamed: D19.2 (A), SW14.2 (B)
unnamed: D20.2 (A), SW15.2 (B)
unnamed: D21.2 (A), SW16.2 (B)
unnamed: D22.2 (A), SW17.2 (B)
unnamed: D23.2 (A), SW18.2 (B)
unnamed: D24.2 (A), SW19.2 (B)
unnamed: D25.2 (A), SW20.2 (B)
unnamed: D26.2 (A), SW21.2 (B)
unnamed: D27.2 (A), SW22.2 (B)
unnamed: D28.2 (A), SW23.2 (B)
unnamed: D29.2 (A), SW24.2 (B)
unnamed: D30.2 (A), SW25.2 (B)
unnamed: D31.2 (A), SW26.2 (B)
unnamed: D32.2 (A), SW27.2 (B)
unnamed: D33.2 (A), SW28.2 (B)
unnamed: D34.2 (A), SW29.2 (B)
unnamed: D35.2 (A), SW30.2 (B)
unnamed: D36.2 (A), SW31.2 (B)
unnamed: D37.2 (A), SW32.2 (B)
unnamed: D38.2 (A), SW33.2 (B)
unnamed: D39.2 (A), SW34.2 (B)
unnamed: D40.2 (A), SW35.2 (B)
unnamed: D41.2 (A), SW36.2 (B)
unnamed: D42.2 (A), SW37.2 (B)
unnamed: D43.2 (A), SW38.2 (B)
unnamed: D44.2 (A), SW39.2 (B)
unnamed: D45.2 (A), SW40.2 (B)
unnamed: D46.2 (A), SW41.2 (B)
unnamed: D47.2 (A), SW42.2 (B)
unnamed: D48.2 (A), SW43.2 (B)
unnamed: D49.2 (A), SW44.2 (B)
unnamed: D50.2 (A), SW45.2 (B)
unnamed: D51.2 (A), SW46.2 (B)
unnamed: D52.2 (A), SW47.2 (B)
unnamed: D53.2 (A), SW48.2 (B)
unnamed: D54.2 (A), SW49.2 (B)
unnamed: D55.2 (A), SW50.2 (B)
unnamed: D56.2 (A), SW51.2 (B)
unnamed: D57.2 (A), SW52.2 (B)
unnamed: D58.2 (A), SW53.2 (B)
unnamed: D59.2 (A), SW54.2 (B)
unnamed: D60.2 (A), SW55.2 (B)
unnamed: D61.2 (A), SW56.2 (B)
unnamed: D62.2 (A), SW57.2 (B)
unnamed: D63.2 (A), SW58.2 (B)
unnamed: D64.2 (A), SW59.2 (B)
unnamed: D65.2 (A), SW60.2 (B)
unnamed: D66.2 (A), SW61.2 (B)
unnamed: D67.2 (A), SW62.2 (B)
unnamed: D68.2 (A), SW63.2 (B)
unnamed: D69.2 (A), SW64.2 (B)
unnamed: D70.2 (A), SW65.2 (B)
unnamed: D71.2 (A), SW66.2 (B)
unnamed: D72.2 (A), SW67.2 (B)
unnamed: D73.2 (A), SW68.2 (B)
unnamed: D74.2 (A), SW69.2 (B)
unnamed: D75.2 (A), SW70.2 (B)
unnamed: D76.2 (A), SW71.2 (B)
unnamed: D77.2 (A), SW72.2 (B)
unnamed: D78.2 (A), SW73.2 (B)
unnamed: D79.2 (A), SW74.2 (B)
unnamed: D80.2 (A), SW75.2 (B)
unnamed: D81.2 (A), SW76.2 (B)
unnamed: D82.2 (A), SW77.2 (B)
unnamed: D83.2 (A), SW78.2 (B)
unnamed: D84.2 (A), SW79.2 (B)
unnamed: D85.2 (A), SW80.2 (B)
unnamed: D86.2 (A), SW81.2 (B)
unnamed: D87.2 (A), SW82.2 (B)
unnamed: D88.2 (A), SW83.2 (B)
unnamed: D89.2 (A), SW84.2 (B)
unnamed: D90.2 (A), SW85.2 (B)
unnamed: D95.2 (A), SW86.2 (B)
unnamed: D96.2 (A), SW87.2 (B)
unnamed: D97.2 (A), SW88.2 (B)
unnamed: D98.2 (A), SW89.2 (B)
unnamed: D99.2 (A), SW90.2 (B)
unnamed: D100.2 (A), SW91.2 (B)
unnamed: D101.2 (A), SW92.2 (B)
unnamed: D102.2 (A), SW93.2 (B)
unnamed: D103.2 (A), SW94.2 (B)
unnamed: D104.2 (A), SW95.2 (B)
unnamed: D105.2 (A), SW96.2 (B)
unnamed: D106.2 (A), SW97.2 (B)
unnamed: D107.2 (A), SW98.2 (B)
unnamed: D108.2 (A), SW99.2 (B)
unnamed: D109.2 (A), SW100.2 (B)
unnamed: D110.2 (A), SW101.2 (B)
unnamed: D111.2 (A), SW102.2 (B)
unnamed: D112.2 (A), SW103.2 (B)
unnamed: D113.2 (A), SW104.2 (B)
unnamed: D114.2 (A), SW105.2 (B)
unnamed: D127.2 (A), L1.2, U22.1 (SW)
unnamed: D128.1 (K), R105.2
unnamed: D129.1 (K), R106.2
unnamed: FB9.1, J8.A4 (VBUS), J8.A9 (VBUS), J8.B4 (VBUS), J8.B9 (VBUS)
unnamed: FB12.1, J9.A4 (VBUS), J9.A9 (VBUS), J9.B4 (VBUS), J9.B9 (VBUS)
unnamed: J6.A5 (CC1), R82.1
unnamed: J6.B5 (CC2), R83.2
unnamed: C160.1, C161.1, J6.S1 (Shield), R79.1
unnamed: C169.1, C171.1, R91.1
unnamed: FB8.1, J7.1 (VBUS)
unnamed: J8.A5 (CC1), R92.1
unnamed: J8.B5 (CC2), R93.2
unnamed: C168.1, C170.1, J8.S1 (Shield), R90.1
unnamed: J9.A5 (CC1), R98.1
unnamed: J9.B5 (CC2), R101.2
unnamed: C192.1, C194.1, J9.S1 (Shield), R97.1
unnamed: R31.2, R39.1, RE2.A
unnamed: R32.2, R40.1, RE2.B
unnamed: R33.2, R41.1, RE3.A
unnamed: R34.2, R42.1, RE3.B
unnamed: R35.2, R43.1, RE4.A
unnamed: R36.2, R44.1, RE4.B
unnamed: R37.2, R45.1, RE5.A
unnamed: R38.2, R46.1, RE5.B
unnamed: R104.2, R108.1
unnamed: R110.1, R111.2
unnamed: RGB1.2 (DOUT), RGB2.4 (DIN)
unnamed: RGB2.2 (DOUT), RGB3.4 (DIN)
unnamed: RGB3.2 (DOUT), RGB4.4 (DIN)
unnamed: RGB4.2 (DOUT), RGB5.4 (DIN)
unnamed: RGB5.2 (DOUT), RGB6.4 (DIN)
unnamed: RGB6.2 (DOUT), RGB7.4 (DIN)
unnamed: RGB7.2 (DOUT), RGB8.4 (DIN)
unnamed: RGB8.2 (DOUT), RGB9.4 (DIN)
unnamed: RGB9.2 (DOUT), RGB10.4 (DIN)
unnamed: RGB10.2 (DOUT), RGB11.4 (DIN)
unnamed: RGB11.2 (DOUT), RGB12.4 (DIN)
unnamed: RGB12.2 (DOUT), RGB13.4 (DIN)
unnamed: RGB13.2 (DOUT), RGB14.4 (DIN)
unnamed: RGB14.2 (DOUT), RGB15.4 (DIN)
unnamed: RGB15.2 (DOUT), RGB16.4 (DIN)
unnamed: RGB16.2 (DOUT), RGB17.4 (DIN)
unnamed: RGB17.2 (DOUT), RGB18.4 (DIN)
unnamed: RGB18.2 (DOUT), RGB19.4 (DIN)
unnamed: RGB19.2 (DOUT), RGB20.4 (DIN)
unnamed: RGB20.2 (DOUT), RGB21.4 (DIN)
unnamed: RGB21.2 (DOUT), RGB22.4 (DIN)
unnamed: RGB22.2 (DOUT), RGB23.4 (DIN)
unnamed: RGB23.2 (DOUT), RGB24.4 (DIN)
unnamed: RGB24.2 (DOUT), RGB25.4 (DIN)
unnamed: RGB25.2 (DOUT), RGB26.4 (DIN)
unnamed: RGB26.2 (DOUT), RGB27.4 (DIN)
unnamed: RGB27.2 (DOUT), RGB28.4 (DIN)
unnamed: RGB28.2 (DOUT), RGB29.4 (DIN)
unnamed: RGB29.2 (DOUT), RGB30.4 (DIN)
unnamed: RGB30.2 (DOUT), RGB31.4 (DIN)
unnamed: RGB31.2 (DOUT), RGB32.4 (DIN)
unnamed: RGB32.2 (DOUT), RGB33.4 (DIN)
unnamed: RGB33.2 (DOUT), RGB34.4 (DIN)
unnamed: RGB34.2 (DOUT), RGB35.4 (DIN)
unnamed: RGB35.2 (DOUT), RGB36.4 (DIN)
unnamed: RGB37.2 (DOUT), RGB38.4 (DIN)
unnamed: RGB38.2 (DOUT), RGB39.4 (DIN)
unnamed: RGB39.2 (DOUT), RGB40.4 (DIN)
unnamed: RGB40.2 (DOUT), RGB41.4 (DIN)
unnamed: RGB41.2 (DOUT), RGB42.4 (DIN)
unnamed: RGB42.2 (DOUT), RGB43.4 (DIN)
unnamed: RGB43.2 (DOUT), RGB44.4 (DIN)
unnamed: RGB44.2 (DOUT), RGB45.4 (DIN)
unnamed: RGB45.2 (DOUT), RGB46.4 (DIN)
unnamed: RGB46.2 (DOUT), RGB47.4 (DIN)
unnamed: RGB47.2 (DOUT), RGB48.4 (DIN)
unnamed: RGB48.2 (DOUT), RGB49.4 (DIN)
unnamed: RGB49.2 (DOUT), RGB50.4 (DIN)
unnamed: RGB50.2 (DOUT), RGB51.4 (DIN)
unnamed: RGB51.2 (DOUT), RGB52.4 (DIN)
unnamed: RGB52.2 (DOUT), RGB53.4 (DIN)
unnamed: RGB53.2 (DOUT), RGB54.4 (DIN)
unnamed: RGB54.2 (DOUT), RGB55.4 (DIN)
unnamed: RGB55.2 (DOUT), RGB56.4 (DIN)
unnamed: RGB56.2 (DOUT), RGB57.4 (DIN)
unnamed: RGB57.2 (DOUT), RGB58.4 (DIN)
unnamed: RGB58.2 (DOUT), RGB59.4 (DIN)
unnamed: RGB59.2 (DOUT), RGB60.4 (DIN)
unnamed: RGB60.2 (DOUT), RGB61.4 (DIN)
unnamed: RGB61.2 (DOUT), RGB62.4 (DIN)
unnamed: RGB62.2 (DOUT), RGB63.4 (DIN)
unnamed: RGB63.2 (DOUT), RGB64.4 (DIN)
unnamed: RGB64.2 (DOUT), RGB65.4 (DIN)
unnamed: RGB65.2 (DOUT), RGB66.4 (DIN)
unnamed: RGB66.2 (DOUT), RGB67.4 (DIN)
unnamed: RGB67.2 (DOUT), RGB68.4 (DIN)
unnamed: RGB68.2 (DOUT), RGB69.4 (DIN)
unnamed: RGB69.2 (DOUT), RGB70.4 (DIN)
unnamed: RGB70.2 (DOUT), RGB71.4 (DIN)
unnamed: RGB71.2 (DOUT), RGB72.4 (DIN)
unnamed: RGB72.2 (DOUT), RGB73.4 (DIN)
unnamed: RGB73.2 (DOUT), RGB74.4 (DIN)
unnamed: RGB74.2 (DOUT), RGB75.4 (DIN)
unnamed: RGB75.2 (DOUT), RGB76.4 (DIN)
unnamed: RGB76.2 (DOUT), RGB77.4 (DIN)
unnamed: RGB77.2 (DOUT), RGB78.4 (DIN)
unnamed: RGB78.2 (DOUT), RGB79.4 (DIN)
unnamed: RGB79.2 (DOUT), RGB80.4 (DIN)
unnamed: RGB80.2 (DOUT), RGB81.4 (DIN)
unnamed: RGB81.2 (DOUT), RGB82.4 (DIN)
unnamed: RGB82.2 (DOUT), RGB83.4 (DIN)
unnamed: RGB83.2 (DOUT), RGB84.4 (DIN)
unnamed: RGB85.2 (DOUT), RGB86.4 (DIN)
unnamed: RGB86.2 (DOUT), RGB87.4 (DIN)
unnamed: RGB87.2 (DOUT), RGB88.4 (DIN)
unnamed: RGB88.2 (DOUT), RGB89.4 (DIN)
unnamed: RGB89.2 (DOUT), RGB90.4 (DIN)
unnamed: RGB90.2 (DOUT), RGB91.4 (DIN)
unnamed: RGB91.2 (DOUT), RGB92.4 (DIN)
unnamed: RGB92.2 (DOUT), RGB93.4 (DIN)
unnamed: RGB93.2 (DOUT), RGB94.4 (DIN)
unnamed: RGB94.2 (DOUT), RGB95.4 (DIN)
unnamed: RGB95.2 (DOUT), RGB96.4 (DIN)
unnamed: RGB96.2 (DOUT), RGB97.4 (DIN)
unnamed: RGB97.2 (DOUT), RGB98.4 (DIN)
unnamed: RGB98.2 (DOUT), RGB99.4 (DIN)
unnamed: RGB99.2 (DOUT), RGB100.4 (DIN)
unnamed: RGB100.2 (DOUT), RGB101.4 (DIN)
unnamed: RGB101.2 (DOUT), RGB102.4 (DIN)
unnamed: RGB102.2 (DOUT), RGB103.4 (DIN)
unnamed: RGB103.2 (DOUT), RGB104.4 (DIN)
unnamed: C213.2, L1.1, SW108.2 (B), U22.4 (EN), U22.5 (IN)
unnamed: R89.1, U16.45 (AUTOENz/HS_SUSPEND)
unnamed: R88.1, U16.40 (FULLPWRMGMTz/SMBA1/SS_UP)
unnamed: R87.1, U16.42 (GANGED/SMBA2/HS_UP)
unnamed: C167.1, U16.50 (GRSTz)
unnamed: R86.1, U16.49 (TEST)
unnamed: R85.1, U16.64 (USB_R1)
unnamed: R96.1, U17.7 (ILM)
unnamed: R102.1, U20.7 (ILM)
unnamed: R105.1, U21.7 (CHRG#)
unnamed: R104.1, U21.2 (PROG)
unnamed: R106.1, U21.6 (STDBY#)
unnamed: R103.2, R107.1, U22.3 (FB)
unnamed: R110.2, U23.2 (CS)
unnamed: Q4.6, U23.3 (OC)
unnamed: Q4.4, U23.1 (OD)
unnamed: C214.2, U23.5 (VCC)

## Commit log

2023-01-04 Updated Readme and switch matrix
2023-01-07 Fixed gitignore
2023-01-20 Testing Shift Register
2023-02-15 Clean code and testing
    Tested keyboard and rotary encoder in a different sketch, tested and working temporary rotary encoder, new schematics for cleaner look in KiCad v7
2023-02-17 Updated schematic
    Added connections between hierarchical sheets, more code testing
2023-02-26 Added RGB control code
2023-03-05 Added testing file for rotary encoders.
2023-03-05 Updated main code to include the new encoder class
2023-07-01 Repository restart
2023-07-03 Rotary encoder working once more. Improved code
2023-07-03 Fixed rotary encoder button debounce
2023-07-12 Rotary encoder, RGB Strip and LCD Screen working
2023-07-12 provisional changes
2023-07-16 changed strings to const char* and effect additions
2023-07-16 LCD not working
2023-07-16 Fix fleeting step in strip config
2023-07-24 Working encoder with actions
2023-07-27 Working encoder and RGB strip with rainbow effect. Initial code for the windows interface.
2023-07-28 added layouts
2023-08-07 working code without keyboard matrix implemented
2023-08-07 uploaded staged changes
2023-08-17 working keyboard prototype code
2023-08-23 Working custom encoder button mapping
2023-08-23 working lcd screen states and counters. Fixed ParamList.
2023-08-24 working prototype
2023-08-24 Created README
2023-09-03 updated schematic
2023-09-08 schematic progress
    added li-po charge circuits and usb hub
2023-09-12 compatibility commit
2023-09-12 Updated USB hub
2023-09-15 bluetooth test added
2023-09-15 Cleaned up and prepped desktop app
    added GUI libraries and OpenGL libraries, along a basic program from The Cherno's YouTube Channel to use as a template.
2023-09-19 Pre initial PCB layout commit
2023-09-19 cleaning commit
2023-09-19 Right layout created
2023-09-20 Finished initial iteration of the Right layout
2023-09-20 better silkscreen
2023-09-21 Started USB hub layout and added footprints
2023-09-29 started hub design
2023-09-29 partially routed discrete components around hub IC
2023-10-01 route most of the differential pairs
2023-10-06 Differential pairs routed on the hub
2023-10-09 restarted hub layout
2023-10-13 More Hub routing
2025-04-02 minor changes
2025-06-02 layout improvements
